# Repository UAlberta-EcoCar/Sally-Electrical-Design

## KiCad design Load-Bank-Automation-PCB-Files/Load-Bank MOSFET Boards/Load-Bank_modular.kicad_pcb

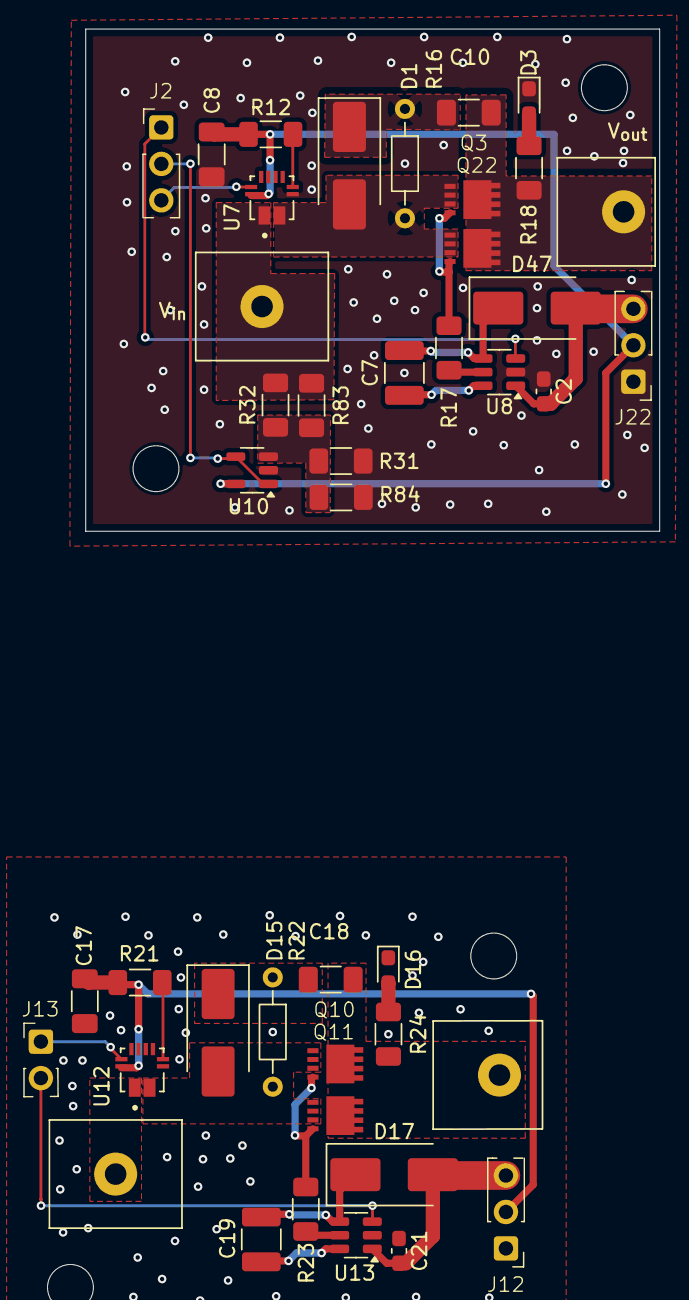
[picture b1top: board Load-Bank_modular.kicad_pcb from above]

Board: 2 copper layers, 40.0 x 35.0 mm, 47 parts (0 on the bottom side), 27 nets.

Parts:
C2, C21: 100n; C_0603_1608Metric_Pad1.08x0.95mm_HandSolder
C7, C19: 4.7u; C_1210_3225Metric_Pad1.33x2.70mm_HandSolder
C8, C17: 100n; C_1206_3216Metric_Pad1.33x1.80mm_HandSolder
C10, C18: 68n; C_1206_3216Metric_Pad1.33x1.80mm_HandSolder
D1, D15, D17, D47: SBR1U200P1; D_SMB_Handsoldering
D3, D16: LED; LED_0603_1608Metric_Pad1.05x0.95mm_HandSolder
H17, H19, H41, H42: MountingHole; MountingHole_3.2mm_M3
H18, H20, H39, H40: MountingHole; TerminalBlock_MetzConnect_360271_1x01_Horizontal_ScrewM3.0_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
J2, J12, J22: Conn_01x03; IDC_PinHeader_1x03_P1.00mm_Vertical
J13: Conn_01x02; IDC_PinHeader_1x02_P1.00mm_Vertical
Q3, Q10, Q11, Q22: GSGN0648; Goodarksemiconductor_PPAK_3x3
R12, R21: 10k; R_1206_3216Metric_Pad1.30x1.75mm_HandSolder
R16, R22: 13k; R_Axial_DIN0204_L3.6mm_D1.6mm_P7.62mm_Horizontal
R17, R23: 39; R_1206_3216Metric_Pad1.30x1.75mm_HandSolder
R18: 20k; R_1206_3216Metric_Pad1.30x1.75mm_HandSolder
R24: 22k; R_1206_3216Metric_Pad1.30x1.75mm_HandSolder
R31, R84: 27k4; R_1206_3216Metric_Pad1.30x1.75mm_HandSolder
R32: 390k; R_1206_3216Metric_Pad1.30x1.75mm_HandSolder
R83: 357k; R_1206_3216Metric_Pad1.30x1.75mm_HandSolder
U7, U12: ACS711KEXLT-31AB-T; XDCR_ACS711KEXLT-15AB-T
U8, U13: IRS10752LTRPBF; SOT-23-6
U10: MCP6006-OTVAO; SOT-23-5

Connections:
+3V3: C8.2, C17.2, J12.2, J22.2, R12.2, R21.2, U7.12 (VCC), U10.5 (V+), U12.12 (VCC)
+12V: C2.2, C21.2, D17.2 (A), D47.2 (A), J12.3, J22.3, U8.1 (V_{cc}), U13.1 (V_{cc})
/MOSFET Board 2/Current_ADC: J13.1, U12.11 (VIOUT)
/MOSFET Board 2/PWM: J13.2, U13.3 (IN)
/MOSFET Board 2/V_{IN}: H18.1, U12.1 (IP+)
/MOSFET Board 2/V_{OUT}: C18.1, H20.1, Q10.3 (S), Q11.3 (S), R24.1
/Mosfet Board 1/Current_ADC: J2.3, U7.11 (VIOUT)
/Mosfet Board 1/PWM: J2.1, U8.3 (IN)
/Mosfet Board 1/V_{IN}: H39.1, R32.1, R83.1, U7.1 (IP+)
/Mosfet Board 1/V_{OUT}: C10.1, H40.1, Q3.3 (S), Q22.3 (S), R18.1
/Mosfet Board 1/Voltage_ADC: J2.2, U10.1, U10.4 (-)
GND: C2.1, C8.1, C17.1, C21.1, D3.1 (K), D16.1 (K), J12.1, J22.1, R31.1, R84.1, U7.5 (GND), U8.2 (COM), U10.2 (V-), U12.5 (GND), U13.2 (COM)
unnamed: D1.2 (A), Q3.1 (D), Q3.2 (G), Q22.1 (D), Q22.2 (G), R16.2, R17.1, U7.3 (IP-)
unnamed: C10.2, D1.1 (K), R16.1
unnamed: D15.2 (A), Q10.1 (D), Q10.2 (G), Q11.1 (D), Q11.2 (G), R22.2, R23.1, U12.3 (IP-)
unnamed: C18.2, D15.1 (K), R22.1
unnamed: D3.2 (A), R18.2
unnamed: D16.2 (A), R24.2
unnamed: C19.1, D17.1 (K), U13.4 (V_{B})
unnamed: C7.1, D47.1 (K), U8.4 (V_{B})
unnamed: R21.1, U12.6 (~FAULT)
unnamed: R23.2, U13.5 (HO)
unnamed: C19.2, U13.6 (V_{s})
unnamed: R12.1, U7.6 (~FAULT)
unnamed: R17.2, U8.5 (HO)
unnamed: C7.2, U8.6 (V_{s})
unnamed: R31.2, R32.2, R83.2, R84.2, U10.3 (+)

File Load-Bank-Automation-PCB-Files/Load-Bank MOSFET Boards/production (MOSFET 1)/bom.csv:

Designator,Footprint,Quantity,Value,LCSC Part #
C10,1206,1,68n,
"C2, C8",0603,2,100n,
C7,1210,1,4.7u,
"D1, D47",D_SMB_Handsoldering,2,SBR1U200P1,
D3,0603,1,LED,
"J2, J22",IDC_PinHeader_1x03_P1.00mm_Vertical,2,Conn_01x03,
"Q22, Q3",Goodarksemiconductor_PPAK_3x3,2,GSGN0648,
R12,1210,1,10k,
R16,R_Axial_DIN0204_L3.6mm_D1.6mm_P7.62mm_Horizontal,1,13k,
R17,1206,1,39,
R18,1210,1,20k,
"R31, R84",1206,2,27k4,
R32,1206,1,390k,
R83,1206,1,357k,
U10,SOT-23-5,1,MCP6006-OTVAO,
U3,Allegro_QFN-12-10-1EP_3x3mm_P0.5mm,1,ACS711xEXLT-31AB,
U8,SOT-23-6,1,IRS10752LTRPBF,

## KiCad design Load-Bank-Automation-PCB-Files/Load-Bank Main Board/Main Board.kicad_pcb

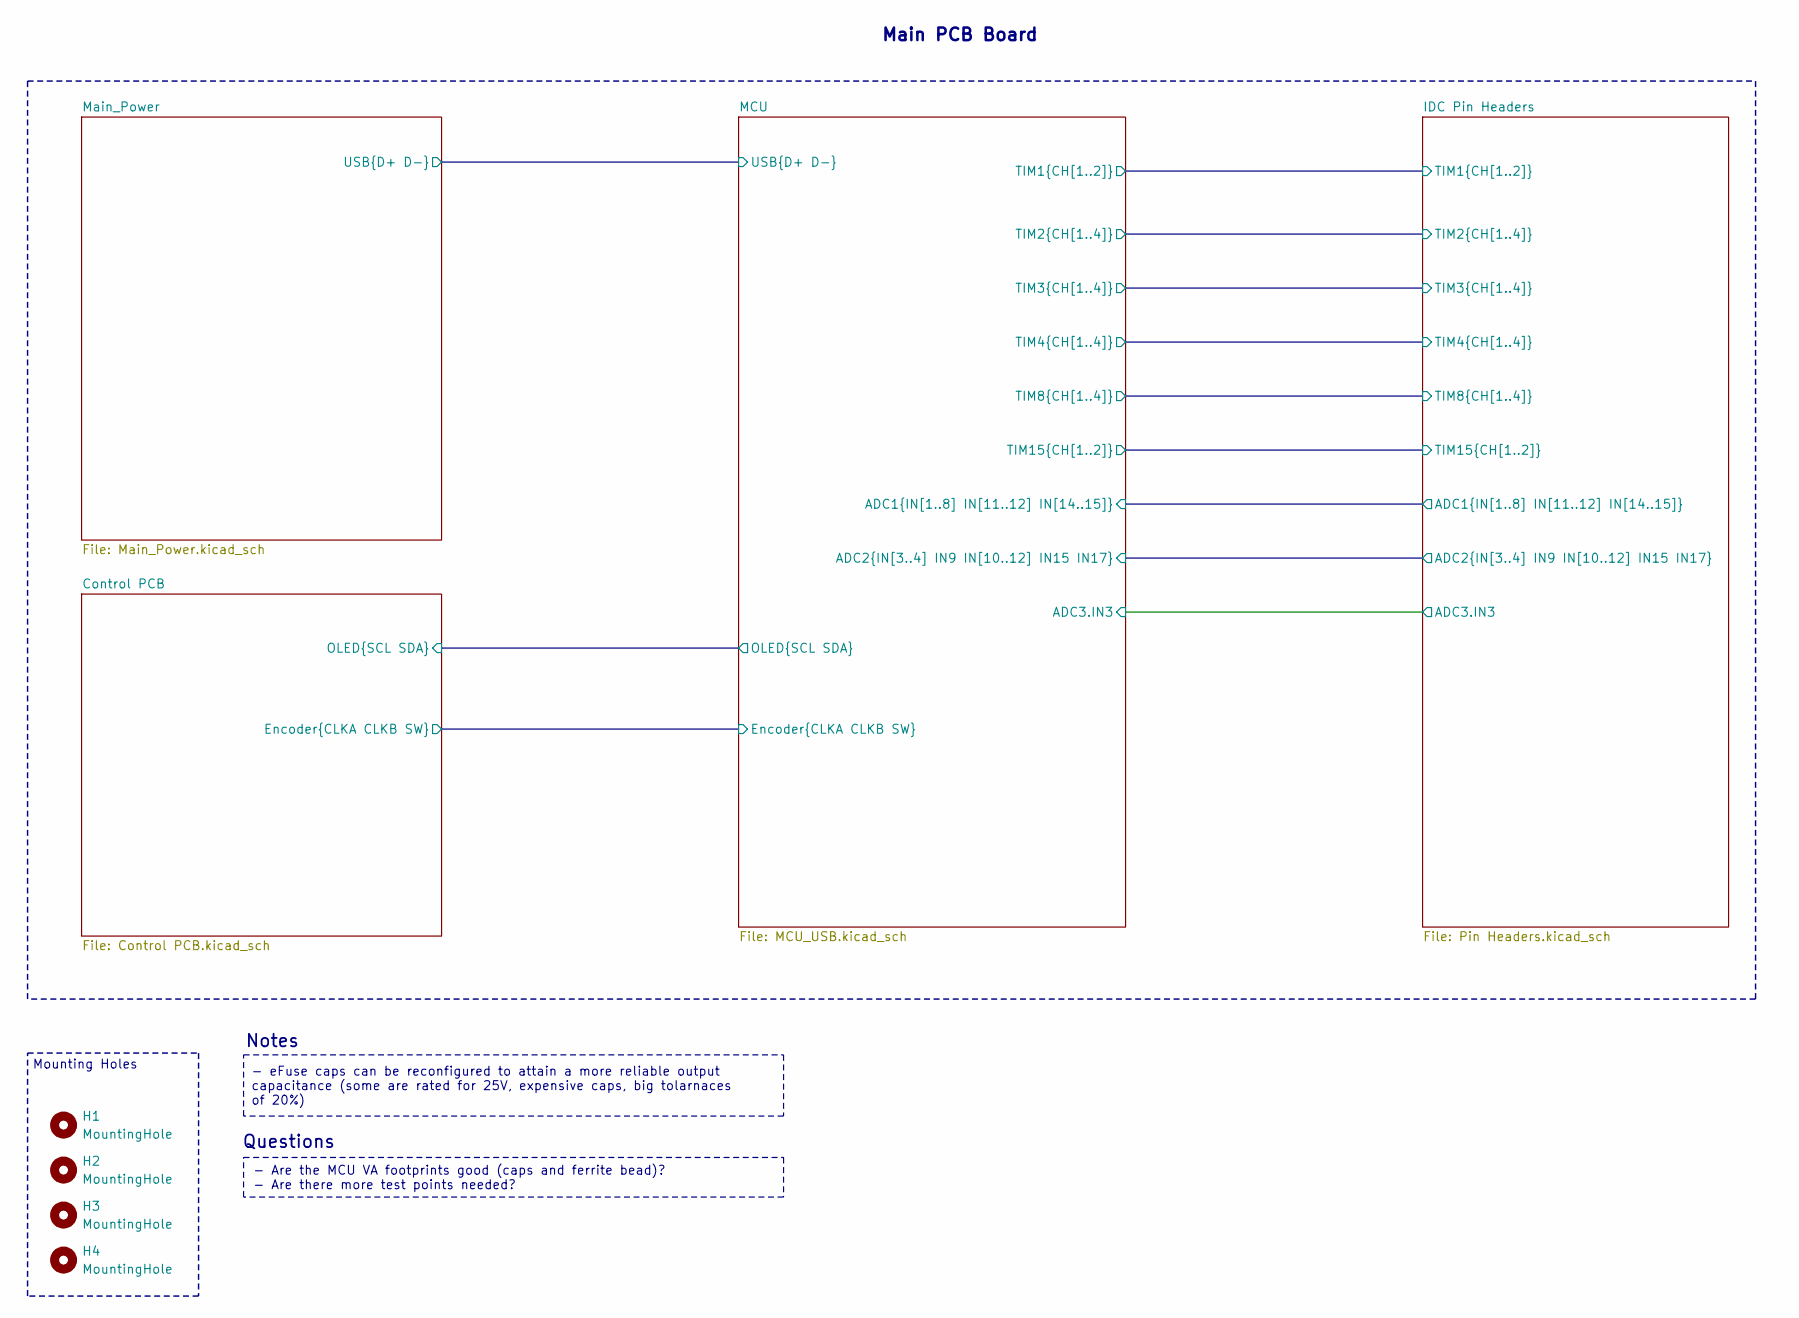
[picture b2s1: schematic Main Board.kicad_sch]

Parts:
H1, H2, H3, H4: MountingHole; MountingHole_3.2mm_M3

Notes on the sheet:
- eFuse caps can be reconfigured to attain a more reliable output capacitance (some are rated for 25V, expensive caps, big tolarnaces of 20%)
Mounting Holes
Main PCB Board
Questions
Notes
- Are the MCU VA footprints good (caps and ferrite bead)? - Are there more test points needed?

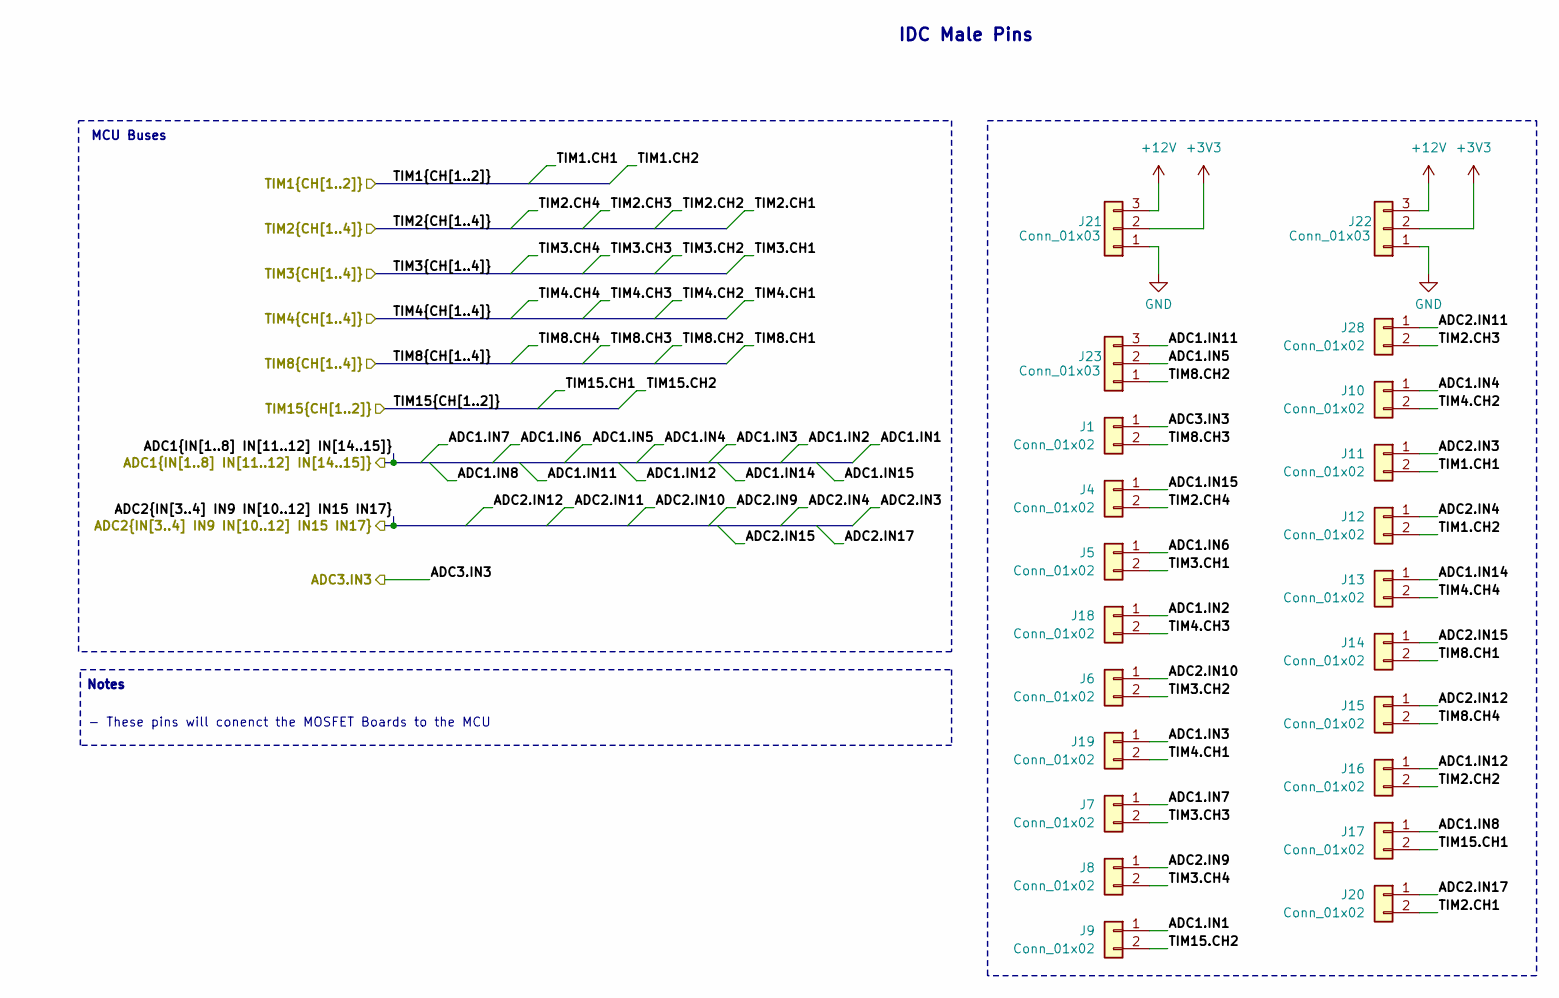
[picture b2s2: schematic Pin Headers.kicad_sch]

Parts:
J1, J4, J5, J6, J7, J8, J9, J10, J11, J12, J13, J14, J15, J16, J17, J18, J19, J20, J28: Conn_01x02; IDC_PinHeader_1x02_P1.00mm_Vertical
J21, J22, J23: Conn_01x03; IDC_PinHeader_1x03_P1.00mm_Vertical

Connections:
+12V: J21.3, J22.3; also elsewhere on the board
/IDC Pin Headers/ADC1.IN1: J9.1; also elsewhere on the board
/IDC Pin Headers/ADC1.IN2: J18.1; also elsewhere on the board
/IDC Pin Headers/ADC1.IN3: J19.1; also elsewhere on the board
/IDC Pin Headers/ADC1.IN4: J10.1; also elsewhere on the board
/IDC Pin Headers/ADC1.IN5: J23.2; also elsewhere on the board
/IDC Pin Headers/ADC1.IN6: J5.1; also elsewhere on the board
/IDC Pin Headers/ADC1.IN7: J7.1; also elsewhere on the board
/IDC Pin Headers/ADC1.IN8: J17.1; also elsewhere on the board
/IDC Pin Headers/ADC1.IN11: J23.3; also elsewhere on the board
/IDC Pin Headers/ADC1.IN12: J16.1; also elsewhere on the board
/IDC Pin Headers/ADC1.IN14: J13.1; also elsewhere on the board
/IDC Pin Headers/ADC1.IN15: J4.1; also elsewhere on the board
/IDC Pin Headers/ADC2.IN3: J11.1; also elsewhere on the board
/IDC Pin Headers/ADC2.IN4: J12.1; also elsewhere on the board
/IDC Pin Headers/ADC2.IN9: J8.1; also elsewhere on the board
/IDC Pin Headers/ADC2.IN10: J6.1; also elsewhere on the board
/IDC Pin Headers/ADC2.IN11: J28.1; also elsewhere on the board
/IDC Pin Headers/ADC2.IN12: J15.1; also elsewhere on the board
/IDC Pin Headers/ADC2.IN15: J14.1; also elsewhere on the board
/IDC Pin Headers/ADC2.IN17: J20.1; also elsewhere on the board
/IDC Pin Headers/ADC3.IN3: J1.1; also elsewhere on the board
/IDC Pin Headers/TIM1.CH1: J11.2; also elsewhere on the board
/IDC Pin Headers/TIM1.CH2: J12.2; also elsewhere on the board
/IDC Pin Headers/TIM2.CH1: J20.2; also elsewhere on the board
/IDC Pin Headers/TIM2.CH2: J16.2; also elsewhere on the board
/IDC Pin Headers/TIM2.CH3: J28.2; also elsewhere on the board
/IDC Pin Headers/TIM2.CH4: J4.2; also elsewhere on the board
/IDC Pin Headers/TIM3.CH1: J5.2; also elsewhere on the board
/IDC Pin Headers/TIM3.CH2: J6.2; also elsewhere on the board
/IDC Pin Headers/TIM3.CH3: J7.2; also elsewhere on the board
/IDC Pin Headers/TIM3.CH4: J8.2; also elsewhere on the board
/IDC Pin Headers/TIM4.CH1: J19.2; also elsewhere on the board
/IDC Pin Headers/TIM4.CH2: J10.2; also elsewhere on the board
/IDC Pin Headers/TIM4.CH3: J18.2; also elsewhere on the board
/IDC Pin Headers/TIM4.CH4: J13.2; also elsewhere on the board
/IDC Pin Headers/TIM8.CH1: J14.2; also elsewhere on the board
/IDC Pin Headers/TIM8.CH2: J23.1; also elsewhere on the board
/IDC Pin Headers/TIM8.CH3: J1.2; also elsewhere on the board
/IDC Pin Headers/TIM8.CH4: J15.2; also elsewhere on the board
/IDC Pin Headers/TIM15.CH1: J17.2; also elsewhere on the board
/IDC Pin Headers/TIM15.CH2: J9.2; also elsewhere on the board
GND: J21.1, J22.1; also elsewhere on the board

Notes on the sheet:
IDC Male Pins
- These pins will conenct the MOSFET Boards to the MCU
Notes
MCU Buses

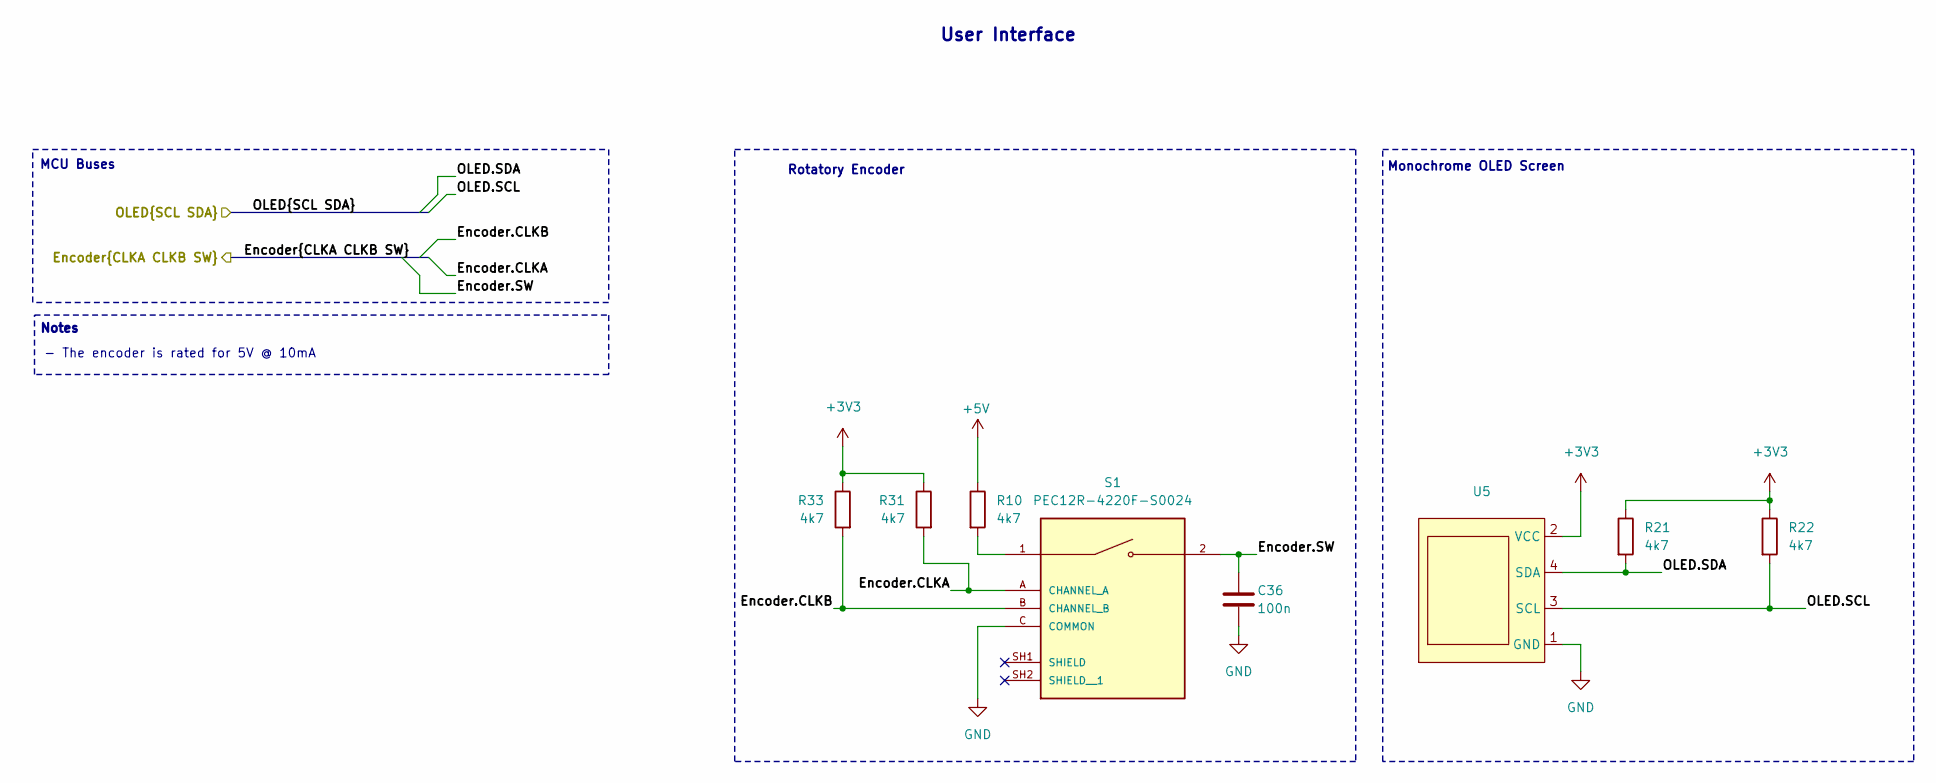
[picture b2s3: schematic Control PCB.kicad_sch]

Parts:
C36: 100n; C_0603_1608Metric_Pad1.08x0.95mm_HandSolder
R10, R21, R22, R31, R33: 4k7; R_1206_3216Metric_Pad1.30x1.75mm_HandSolder
S1: PEC12R-4220F-S0024; XDCR_PEC12R-4220F-S0024; PARTREV 07/21
U5: Display_128x64_096_I2C

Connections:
+5V: R10.1; also elsewhere on the board
/Control PCB/Encoder.CLKA: R31.2, S1.A (CHANNEL_A); also elsewhere on the board
/Control PCB/Encoder.CLKB: R33.2, S1.B (CHANNEL_B); also elsewhere on the board
/Control PCB/Encoder.SW: C36.1, S1.2; also elsewhere on the board
/Control PCB/OLED.SCL: R22.2, U5.3 (SCL); also elsewhere on the board
/Control PCB/OLED.SDA: R21.2, U5.4 (SDA); also elsewhere on the board
GND: C36.2, S1.C (COMMON), U5.1 (GND); also elsewhere on the board
unnamed: R10.2, S1.1

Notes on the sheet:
Rotatory Encoder
MCU Buses
Monochrome OLED Screen
Notes
User Interface
- The encoder is rated for 5V @ 10mA

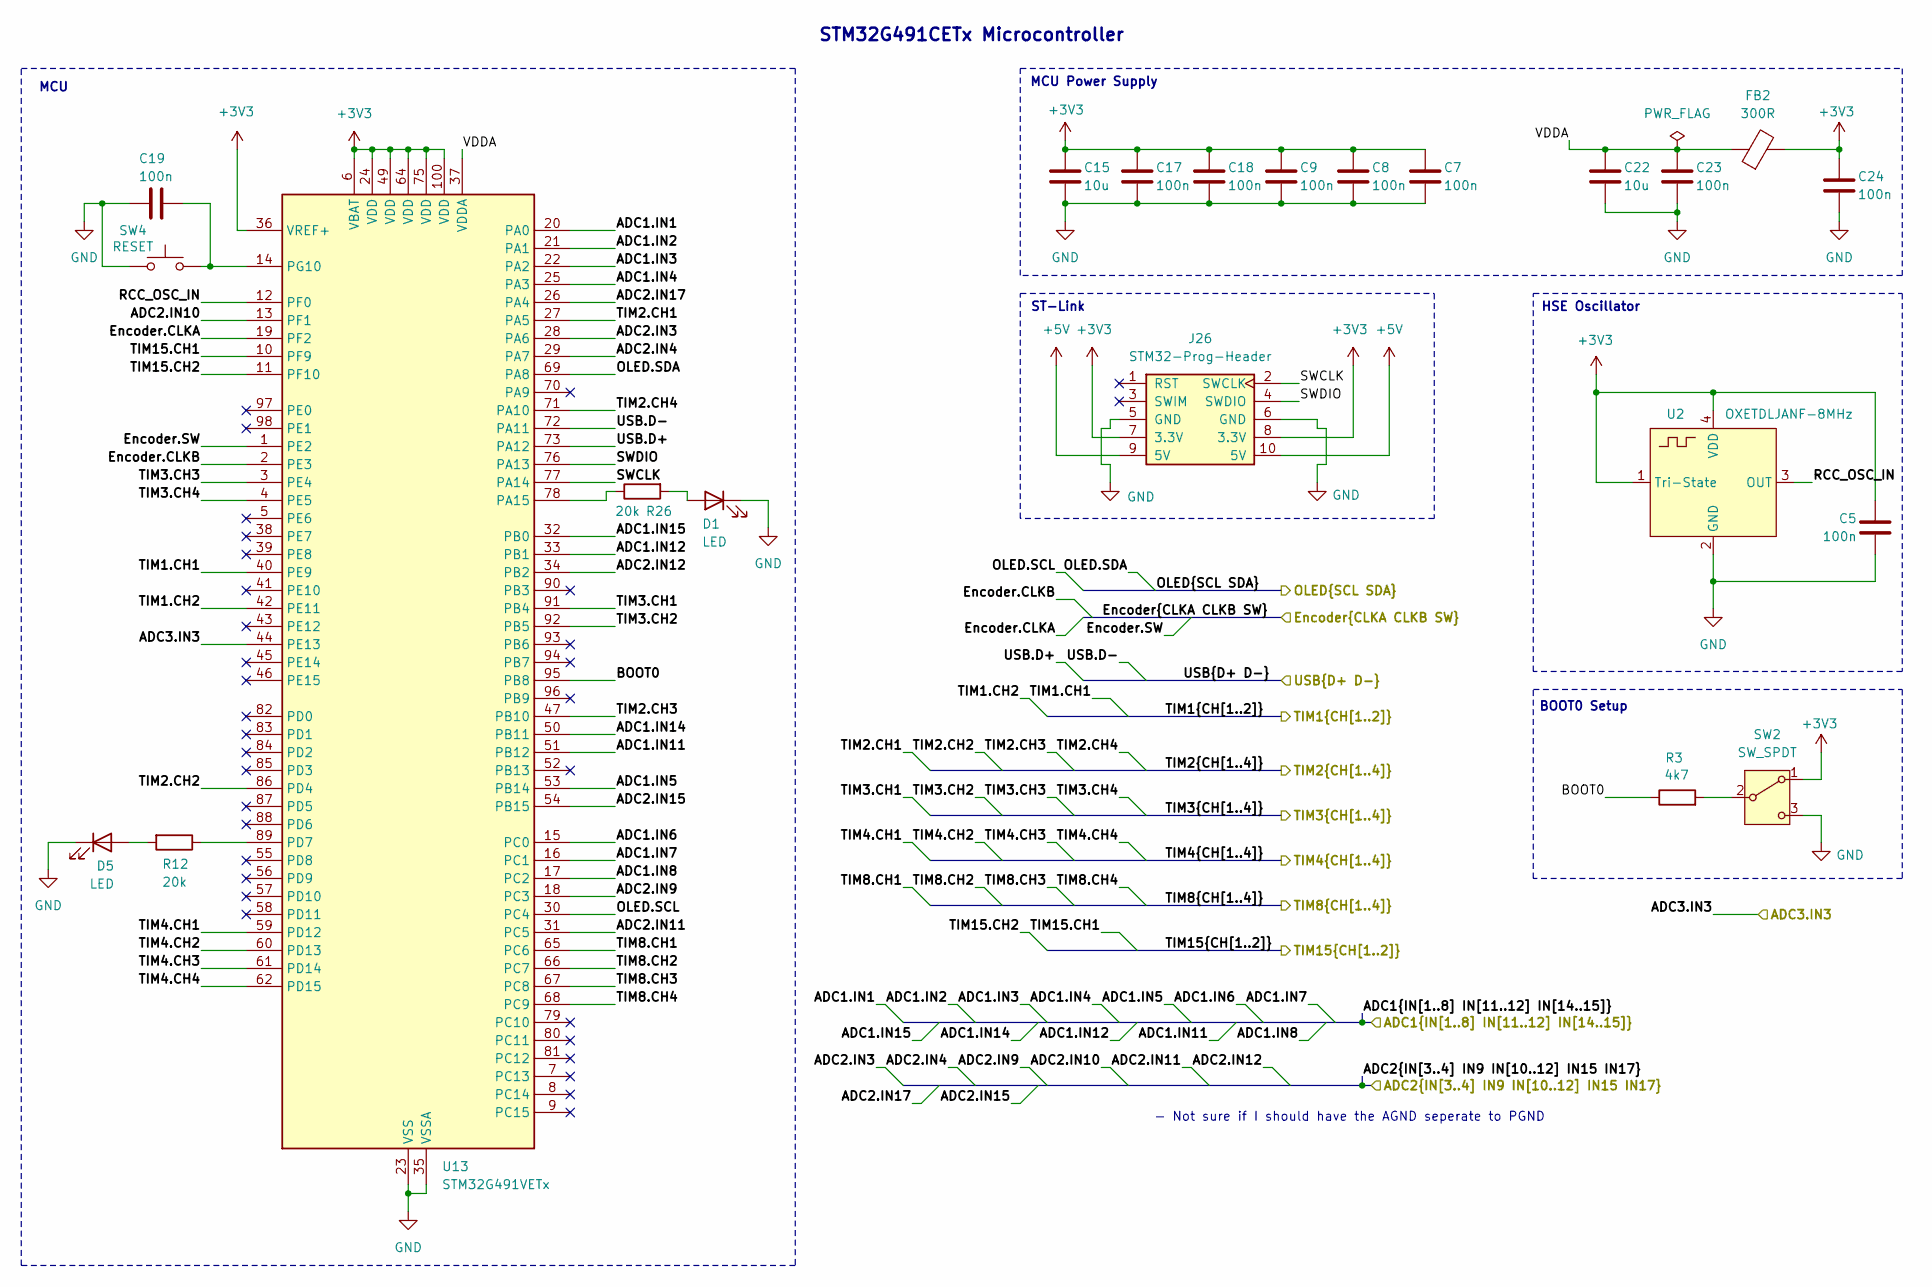
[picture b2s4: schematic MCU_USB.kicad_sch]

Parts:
C5, C7, C8, C9, C17, C18, C19, C23, C24: 100n; C_0603_1608Metric_Pad1.08x0.95mm_HandSolder
C15, C22: 10u; C_0805_2012Metric_Pad1.18x1.45mm_HandSolder
D1, D5: LED; LED_0603_1608Metric
FB2: 300R; R_0603_1608Metric_Pad0.98x0.95mm_HandSolder
J26: STM32-Prog-Header; IDC-STM32-Prog-Header_2x05_P2.54mm_Vertical
R3: 4k7; R_1206_3216Metric_Pad1.30x1.75mm_HandSolder
R12, R26: 20k; R_0603_1608Metric_Pad0.98x0.95mm_HandSolder
SW2: SW_SPDT; SW_SPDT_PCM12
SW4: RESET; SW_PUSH_6mm
U2: OXETDLJANF-8MHz
U13: STM32G491VETx; LQFP-100_14x14mm_P0.5mm

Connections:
+5V: J26.9 (5V), J26.10 (5V); also elsewhere on the board
/Control PCB/Encoder.CLKA: U13.19 (PF2); also elsewhere on the board
/Control PCB/Encoder.CLKB: U13.2 (PE3); also elsewhere on the board
/Control PCB/Encoder.SW: U13.1 (PE2); also elsewhere on the board
/Control PCB/OLED.SCL: U13.30 (PC4); also elsewhere on the board
/Control PCB/OLED.SDA: U13.69 (PA8); also elsewhere on the board
/IDC Pin Headers/ADC1.IN1: U13.20 (PA0); also elsewhere on the board
/IDC Pin Headers/ADC1.IN2: U13.21 (PA1); also elsewhere on the board
/IDC Pin Headers/ADC1.IN3: U13.22 (PA2); also elsewhere on the board
/IDC Pin Headers/ADC1.IN4: U13.25 (PA3); also elsewhere on the board
/IDC Pin Headers/ADC1.IN5: U13.53 (PB14); also elsewhere on the board
/IDC Pin Headers/ADC1.IN6: U13.15 (PC0); also elsewhere on the board
/IDC Pin Headers/ADC1.IN7: U13.16 (PC1); also elsewhere on the board
/IDC Pin Headers/ADC1.IN8: U13.17 (PC2); also elsewhere on the board
/IDC Pin Headers/ADC1.IN11: U13.51 (PB12); also elsewhere on the board
/IDC Pin Headers/ADC1.IN12: U13.33 (PB1); also elsewhere on the board
/IDC Pin Headers/ADC1.IN14: U13.50 (PB11); also elsewhere on the board
/IDC Pin Headers/ADC1.IN15: U13.32 (PB0); also elsewhere on the board
/IDC Pin Headers/ADC2.IN3: U13.28 (PA6); also elsewhere on the board
/IDC Pin Headers/ADC2.IN4: U13.29 (PA7); also elsewhere on the board
/IDC Pin Headers/ADC2.IN9: U13.18 (PC3); also elsewhere on the board
/IDC Pin Headers/ADC2.IN10: U13.13 (PF1); also elsewhere on the board
/IDC Pin Headers/ADC2.IN11: U13.31 (PC5); also elsewhere on the board
/IDC Pin Headers/ADC2.IN12: U13.34 (PB2); also elsewhere on the board
/IDC Pin Headers/ADC2.IN15: U13.54 (PB15); also elsewhere on the board
/IDC Pin Headers/ADC2.IN17: U13.26 (PA4); also elsewhere on the board
/IDC Pin Headers/ADC3.IN3: U13.44 (PE13); also elsewhere on the board
/IDC Pin Headers/TIM1.CH1: U13.40 (PE9); also elsewhere on the board
/IDC Pin Headers/TIM1.CH2: U13.42 (PE11); also elsewhere on the board
/IDC Pin Headers/TIM2.CH1: U13.27 (PA5); also elsewhere on the board
/IDC Pin Headers/TIM2.CH2: U13.86 (PD4); also elsewhere on the board
/IDC Pin Headers/TIM2.CH3: U13.47 (PB10); also elsewhere on the board
/IDC Pin Headers/TIM2.CH4: U13.71 (PA10); also elsewhere on the board
/IDC Pin Headers/TIM3.CH1: U13.91 (PB4); also elsewhere on the board
/IDC Pin Headers/TIM3.CH2: U13.92 (PB5); also elsewhere on the board
/IDC Pin Headers/TIM3.CH3: U13.3 (PE4); also elsewhere on the board
/IDC Pin Headers/TIM3.CH4: U13.4 (PE5); also elsewhere on the board
/IDC Pin Headers/TIM4.CH1: U13.59 (PD12); also elsewhere on the board
/IDC Pin Headers/TIM4.CH2: U13.60 (PD13); also elsewhere on the board
/IDC Pin Headers/TIM4.CH3: U13.61 (PD14); also elsewhere on the board
/IDC Pin Headers/TIM4.CH4: U13.62 (PD15); also elsewhere on the board
/IDC Pin Headers/TIM8.CH1: U13.65 (PC6); also elsewhere on the board
/IDC Pin Headers/TIM8.CH2: U13.66 (PC7); also elsewhere on the board
/IDC Pin Headers/TIM8.CH3: U13.67 (PC8); also elsewhere on the board
/IDC Pin Headers/TIM8.CH4: U13.68 (PC9); also elsewhere on the board
/IDC Pin Headers/TIM15.CH1: U13.10 (PF9); also elsewhere on the board
/IDC Pin Headers/TIM15.CH2: U13.11 (PF10); also elsewhere on the board
/MCU/BOOT0: R3.1, U13.95 (PB8)
/MCU/RCC_OSC_IN: U2.3 (OUT), U13.12 (PF0)
/MCU/SWCLK: J26.2 (SWCLK), U13.77 (PA14)
/MCU/SWDIO: J26.4 (SWDIO), U13.76 (PA13)
/MCU/USB.D+: U13.73 (PA12); also elsewhere on the board
/MCU/USB.D-: U13.72 (PA11); also elsewhere on the board
GND: C5.2, C7.2, C8.2, C9.2, C15.2, C17.2, C18.2, C19.1, C22.2, C23.2, C24.2, D1.1 (K), D5.1 (K), J26.5 (GND), J26.6 (GND), SW2.3 (C), SW4.1, U2.2 (GND), U13.23 (VSS), U13.35 (VSSA), U13.48 (VSS), U13.63 (VSS), U13.74 (VSS), U13.99 (VSS); also elsewhere on the board
unnamed: D1.2 (A), R26.2
unnamed: D5.2 (A), R12.2
unnamed: R3.2, SW2.2 (B)
unnamed: R26.1, U13.78 (PA15)
unnamed: R12.1, U13.89 (PD7)
unnamed: C19.2, SW4.2, U13.14 (PG10)

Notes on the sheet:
MCU
STM32G491CETx Microcontroller
MCU Power Supply
BOOT0 Setup
HSE Oscillator
- Not sure if I should have the AGND seperate to PGND
ST-Link

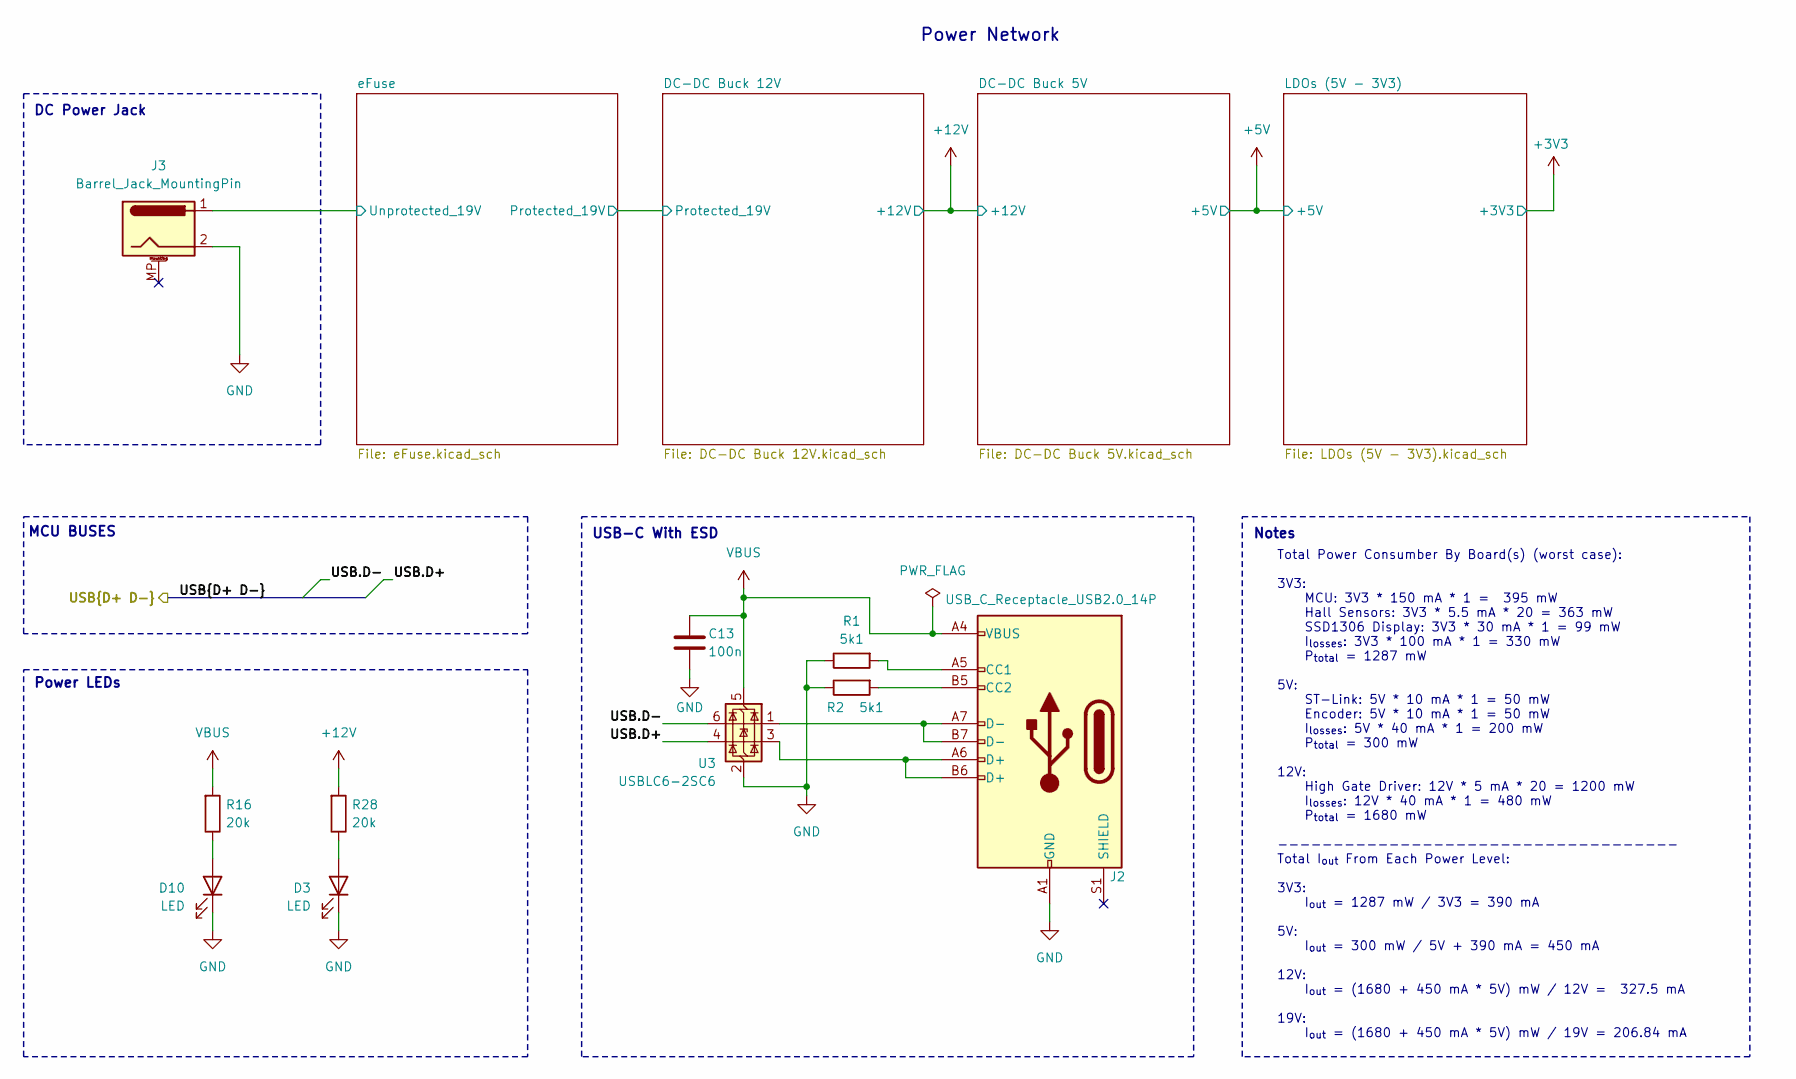
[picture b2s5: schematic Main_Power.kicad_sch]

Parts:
C13: 100n; C_0603_1608Metric_Pad1.08x0.95mm_HandSolder
D3, D10: LED; LED_0603_1608Metric
J2: USB_C_Receptacle_USB2.0_14P; USB_C_Receptacle_GCT_USB4105-xx-A_16P_TopMnt_Horizontal
J3: Barrel_Jack_MountingPin; BarrelJack_TENSILITY_54-00130_Horizontal
R1, R2: 5k1; R_1210_3225Metric_Pad1.30x2.65mm_HandSolder
R16, R28: 20k; R_0603_1608Metric_Pad0.98x0.95mm_HandSolder
U3: USBLC6-2SC6; SOT-23-6

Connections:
+12V: R28.2; also elsewhere on the board
/MCU/USB.D+: U3.4 (I/O2); also elsewhere on the board
/MCU/USB.D-: U3.6 (I/O1); also elsewhere on the board
/Main_Power/eFuse/Unprotected_19V: J3.1; also elsewhere on the board
GND: C13.2, D3.1 (K), D10.1 (K), J2.A1 (GND), J2.A12 (GND), J2.B1 (GND), J2.B12 (GND), J3.2, R1.1, R2.1, U3.2 (GND); also elsewhere on the board
unnamed: D3.2 (A), R28.1
unnamed: D10.2 (A), R16.1
unnamed: J2.A5 (CC1), R1.2
unnamed: J2.B5 (CC2), R2.2
unnamed: J2.A6 (D+), J2.B6 (D+), U3.3 (I/O2)
unnamed: J2.A7 (D-), J2.B7 (D-), U3.1 (I/O1)
VBUS: C13.1, J2.A4 (VBUS), J2.A9 (VBUS), J2.B4 (VBUS), J2.B9 (VBUS), R16.2, U3.5 (VBUS); also elsewhere on the board

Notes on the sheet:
Power Network
DC Power Jack
Notes
USB-C With ESD
MCU BUSES
Total Power Consumber By Board(s) (worst case): 3V3: MCU: 3V3 * 150 mA * 1 = 395 mW Hall Sensors: 3V3 * 5.5 mA * 20 = 363 mW SSD1306 Display: 3V3 * 30 mA * 1 = 99 mW I_{losses}: 3V3 * 100 mA * 1 = 330 mW P_{total} = 1287 mW 5V: ST-Link: 5V * 10 mA * 1 = 50 mW Encoder: 5V * 10 mA * 1 = 50 mW I_{loss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
Power LEDs

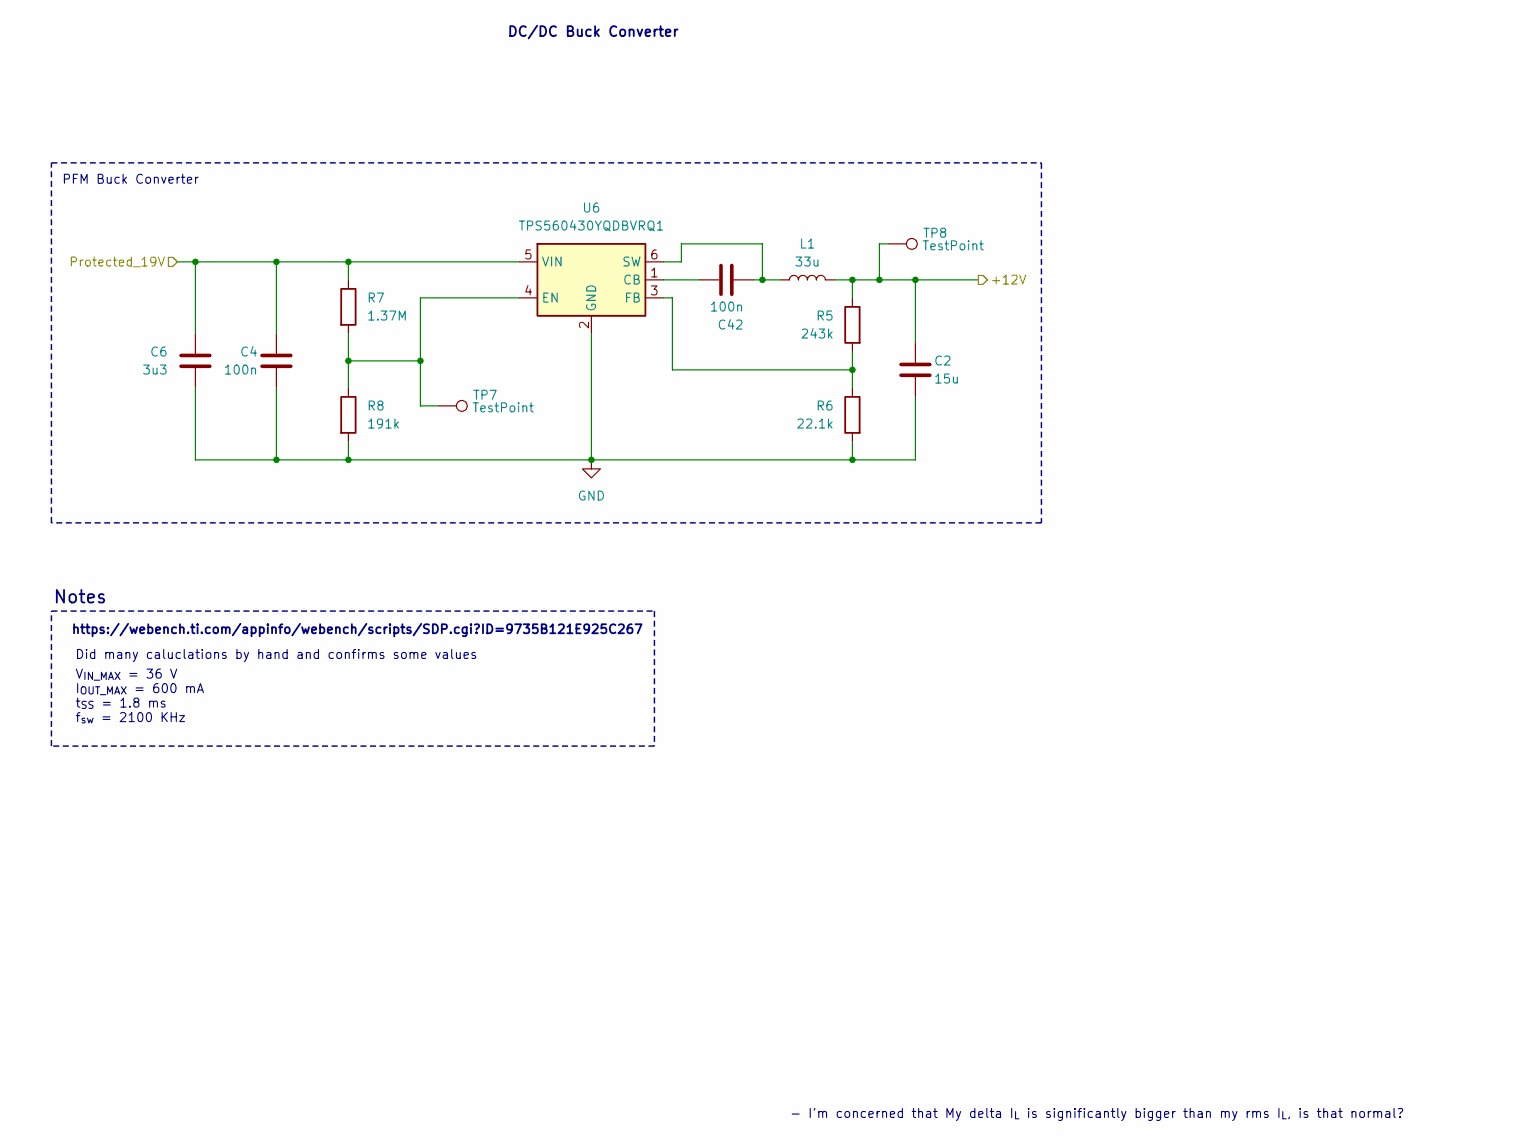
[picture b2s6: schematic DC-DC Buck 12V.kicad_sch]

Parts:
C2: 15u; C_1206_3216Metric_Pad1.33x1.80mm_HandSolder
C4, C42: 100n; C_0603_1608Metric_Pad1.08x0.95mm_HandSolder
C6: 3u3; C_0805_2012Metric_Pad1.18x1.45mm_HandSolder
L1: 33u; L_Bourns_SDR0403
R5: 243k; R_0402_1005Metric_Pad0.72x0.64mm_HandSolder
R6: 22.1k; R_0402_1005Metric_Pad0.72x0.64mm_HandSolder
R7: 1.37M; R_0402_1005Metric_Pad0.72x0.64mm_HandSolder
R8: 191k; R_0402_1005Metric_Pad0.72x0.64mm_HandSolder
TP7, TP8: TestPoint; TestPoint_Pad_D1.0mm
U6: TPS560430YQDBVRQ1; SOT-23-6

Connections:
+12V: C2.1, L1.2, R5.1, TP8.1; also elsewhere on the board
/Main_Power/DC-DC Buck 12V/Protected_19V: C4.1, C6.1, R7.1, U6.5 (VIN); also elsewhere on the board
GND: C2.2, C4.2, C6.2, R6.2, R8.2, U6.2 (GND); also elsewhere on the board
unnamed: C42.1, U6.1 (CB)
unnamed: R7.2, R8.1, TP7.1, U6.4 (EN)
unnamed: R5.2, R6.1, U6.3 (FB)
unnamed: C42.2, L1.1, U6.6 (SW)

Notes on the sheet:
Did many caluclations by hand and confirms some values
V_{IN_MAX} = 36 V I_{OUT_MAX} = 600 mA t_{SS} = 1.8 ms f_{sw} = 2100 KHz
- I'm concerned that My delta I_{L} is significantly bigger than my rms I_{L}, is that normal?
DC/DC Buck Converter
Notes
https://webench.ti.com/appinfo/webench/scripts/SDP.cgi?ID=9735B121E925C267
PFM Buck Converter
